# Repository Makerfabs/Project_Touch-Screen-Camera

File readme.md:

# ESP32 3.5" TFT Touch with Camera

```c++
/*
Version:		V6.2
Author:			Vincent
Create Date:	2020/8/19
Note:
	V6.2 : Change Wiki link.
	V6.1 : Update firmware add camera config faq.
	V6.0 : Add WiFi bulletin board demo
	V5.0 : Add Environment Expansion Board
	V4.1 : Add 1 show example.
	V4.0 : Add 4 show example.
	V3.4 : Thanks Lovyan03's change. Greatly speed up the rendering process.
	V3.3 : Change UI direction.
	V3.2 : Added the ability to upload photos to PC through WiFi. 
	V3.1 : Replace the picture with the new hardware.
	V3.0 : Delete many useless code. Add FAQ.
	V2.0 : Change ILI9488 driver,use LovyanGFX lib.Ten times faster than before!!!
	
*/
```
[ESP32 Touch Camera](https://www.youtube.com/watch?v=zWUy4gcwMs4&feature=youtu.be)

[toc]

# Makerfabs

[Makerfabs home page](https://www.makerfabs.com/)

[Makerfabs Wiki](https://wiki.makerfabs.com/)

# ESP32 3.5" TFT Touch with Camera

## Introduce

Product link ：[ ESP32 Touch Camera(Resistive)](https://www.makerfabs.com/esp32-3.5-inch-tft-touch-resistive-with-camera.html) 

Product link ：[ ESP32 Touch Camera(Capacitive)](https://www.makerfabs.com/esp32-3.5-inch-tft-touch-capacitive-with-camera.html) 

Wiki link ：[ESP32 3.5" TFT Touch with Camera](https://wiki.makerfabs.com/ESP32_3.5_TFT_Touch_with_Camera.html) 

The ESP32 Touch Camera use ILI9488 screen, which comes with resistive or capacitive screens. Have an OV2640 camera and SD card slot. It can be used as a webcam, an electronic album, or a digital camera. Support for Arduino and MicroPython. 

## Feature

- Integrated ESP32 2.4G WiFi and Bluetooth.
- Micro SD card slot on board.
- Input 5.0V Type-C USB .
- OV2640 is a 1/4 inch CMOS UXGA (1632*1232) image sensor manufactured by OmniVision.
- LCD 3.5 inch Amorphous-TFT-LCD (Thin Film Transistor Liquid Crystal Display) for mobile-phone or handy electrical equipments.
- NS2009 is A 4-wire resistive touch screen control circuit with I2C interface, which contains A 12-bit resolution A/D converter.

- The FT6X36 Series ICs are single-chip capacitive touch panel controller IC with a built-in 16 bit enhanced Micro-controller unit (MCU).

# Project

## Related projects

[ESP32 2048 GAME](https://github.com/Makerfabs/Project_ESP32-2048GAME)

Implement a 2048 game on "ESP32 Touch Camera". 

[ESP32 Flappy Bird](https://github.com/Makerfabs/Project_ESP32-Flappy-Bird)

Implement a Flappy Bird game on "ESP32 Touch Camera". 

## Project introduction

Four projects were implemented : "Camera", "Touch_Draw", "SD2TFT" and "Receive WiFi Video".

### Camera_V2

- Take photos with OV2640 camera and preview in real-time on TFT screen.
- You can save photos to an SD card.
- Photos taken can be viewed through the TFT screen.

### Touch_Draw_V2

- Use your hand or stylus (resistance screen) to draw on the screen.

### SD2TFT 

- Display pictures from SD card.
- Loop back the images in the SD card.

### Receive WiFi Video

Transmit the contents of the monitor to the TFT screen via Wifi.A host computer software is provided to box select the areas of the screen that need to be transferred.

Change from [MakePython ESP32 Color LCD で 動画をWiFi受信](https://homemadegarbage.com/makerfabs05)

- Upload file : "/Project_Touch-Screen-Camra/ESP32_ScreenShotReceiver-master/ScreenShotReceiver/ScreenShotReceiver.ino"
- Open "/Project_Touch-Screen-Camra/ESP32_ScreenShotReceiver-master/ScreenShotSender.exe"
- Input IP on the screen.

- Push connect.
- Start share your screen to TFT.

## Compiler Options

**If you have any questions，such as how to install the development board, how to download the code, how to install the library. Please refer to :[Makerfabs_FAQ](https://github.com/Makerfabs/Makerfabs_FAQ)**

- Install board : ESP32 , select ESP32 version 1.0.6!!!!!!! After 2.0.0 version can't run successfully.
- **2022/4/28 Add：I don't know which libraries I updated, 1.0.6 compiles but doesn't drive the camera properly, rolling back the ESP32 version to 1.0.5 works fine.**
- Install library : LovyanGFX library. (SD2TFT is use a different GFX lib, depend on Adafruit_GFX. )
- Edit the code based on the touch screen. If you use resistive screen, choice NS2009_TOUCH. If you use capacitive screen, choice FT6236_TOUCH.

```c++
#define NS2009_TOUCH        //Resistive screen driver    
//#define FT6236_TOUCH      //Capacitive screen driver

#ifdef NS2009_TOUCH
#include "NS2009.h"
const int i2c_touch_addr = NS2009_ADDR;
#endif

#ifdef FT6236_TOUCH
#include "FT6236.h"
const int i2c_touch_addr = TOUCH_I2C_ADD;
#endif

```

- Upload codes, select "ESP32 Wrover Module" and "Huge APP"

- Insert a Micro SD card into ESP32 Touch Camera.

## How To Use ESP32 Touch Camera

- Open the serial port monitor after uploading the code.
- Serial port will return initialization information, pay attention to see if there is any error.

```txt
14:48:49.096 -> ets Jun  8 2016 00:22:57
14:48:49.096 -> 
14:48:49.096 -> rst:0x1 (POWERON_RESET),boot:0x17 (SPI_FAST_FLASH_BOOT)
14:48:49.096 -> configsip: 0, SPIWP:0xee
14:48:49.096 -> clk_drv:0x00,q_drv:0x00,d_drv:0x00,cs0_drv:0x00,hd_drv:0x00,wp_drv:0x00
14:48:49.096 -> mode:DIO, clock div:1
14:48:49.096 -> load:0x3fff0018,len:4
14:48:49.096 -> load:0x3fff001c,len:1100
14:48:49.096 -> load:0x40078000,len:9232
14:48:49.096 -> load:0x40080400,len:6400
14:48:49.096 -> entry 0x400806a8
14:48:50.641 -> ILI9488 Test!
14:48:50.641 -> I2C device found at address 0x38  !
14:48:50.675 -> Card Mount Successed
14:48:50.675 -> SD init over.
14:48:51.397 -> TFT init over.
14:49:10.660 -> Image name：/0write.bmp
14:49:13.859 -> Image name：/1write.bmp

```

- If the SD card cannot be mounted on return, you need to re-insert the SD card.
- If everything is normal, the camera interface will be displayed.

- Press the camera button to take photos automatically.
- Click on the previous photo to show the last photo saved on the SD card.

- Pressing to show the last photo will stop the camera acquisition. To restore the preview, press open Stream.
- Restore stream mode to take photos again.
- You can unplug your SD card and plug it into your computer to view your photos.

## V3.2 Upload photos via WiFi
Added the function of sending photos to PC via HTTP protocol by post method.
- Remove comments before WIFI_MODE

```c++
#define WIFI_MODE
```
- Set the wifi ssid and password.

```c++
// wait for WiFi connection
WiFi.mode(WIFI_STA);
WiFi.begin("Makerfabs", "20160704");
```
- Upload code to ESP32 camera.
- Run the server.py  on PC side.(Make sure to run in the directory server.py, otherwise the upload path cannot be found.)

- Every time you click to show the last photo, it will be automatically uploaded.

- In a few seconds, the picture will be uploaded to the Upload folder.
- V3.3  :  The UI has changed, but the functionality remains the same.

## V4.0 Show Example

Add 4 example in /Project_Touch-Screen-Camra/example

- Aht10 show
- HCSR04 meter
- Web button
- Wind speed show

These examples depend on TFT_eSPI library. You must set "User_Setup.h".
Set screen type.

```c++
// Only define one driver, the other ones must be commented out
//#define ILI9341_DRIVER
//#define ST7735_DRIVER      // Define additional parameters below for this display
//#define ILI9163_DRIVER     // Define additional parameters below for this display
//#define S6D02A1_DRIVER
//#define RPI_ILI9486_DRIVER // 20MHz maximum SPI
//#define HX8357D_DRIVER
//#define ILI9481_DRIVER
//#define ILI9486_DRIVER
#define ILI9488_DRIVER     // WARNING: Do not connect ILI9488 display SDO to MISO if other devices share the SPI bus (TFT SDO does NOT tristate when CS is high)
//#define ST7789_DRIVER      // Full configuration option, define additional parameters below for this display
//#define ST7789_2_DRIVER    // Minimal configuration option, define additional parameters below for this display

// For ST7789, ST7735, ILI9163 and GC9A01 ONLY, define the pixel width and height in portrait orientation
// #define TFT_WIDTH  80
// #define TFT_WIDTH  128
// #define TFT_WIDTH  172 // ST7789 172 x 320
//#define TFT_WIDTH  240 // ST7789 240 x 240 and 240 x 320
#define TFT_WIDTH  320
// #define TFT_HEIGHT 160
// #define TFT_HEIGHT 128
// #define TFT_HEIGHT 240 // ST7789 240 x 240
// #define TFT_HEIGHT 320 // ST7789 240 x 320
//#define TFT_HEIGHT 240 // GC9A01 240 x 240
#define TFT_HEIGHT 480

```
And set pins.

```c++
// For 3.5" 9488
// The hardware SPI can be mapped to any pins

#define TFT_MISO 12
#define TFT_MOSI 13
#define TFT_SCLK 14
#define TFT_CS   15  // Chip select control pin
#define TFT_DC    33  // Data Command control pin
#define TFT_RST   26  // Reset pin (could connect to RST pin)

```

## V4.1 Show Example

Add environment monitoring module demo.

- Line chart

## V6.0 WiFi bulletin board Demo

Added a WiFi bulletin board app. You can upload and browse files in the SD card through the web page. And the latest uploaded BMP or TXT display on the 3.5-inch screen.

- Library Install：[esp32-micro-sdcard](https://github.com/nhatuan84/esp32-micro-sdcard) and [esp32-webserver](https://github.com/nhatuan84/esp32-webserver)
- Upload .\example\wifi_img\wifi_img.ino
- Insert the SD card and power on.
- Enter the IP address on the screen in your browser.

- Select TXT or BMP to be uploaded. BMP must be 480 x 320 pixels, 24 bits.

- Upload.
- Wait seconds, the content is displayed on the screen.

## FAQ

### Q: Can't Upload!

A: Switch to a good USB cable. Poor USB cable quality can cause ESP32 to reboot or fail to upload. Open the serial monitor, observe serial port information.

### Q: The screen is white!

A: The SD card was not mounted successfully, so the program goes into an endless loop. Re-insert the SD card and restart it. Open the serial monitor,  The serial port will display the work log.

### Q: It doesn't show the picture that was just taken!

A: It may be that after shooting, the SD card was not in good contact, so it could not be stored in the SD card. Playback photos are read inside the SD card photos. Re-insert the SD card and restart it.

### Q: Other questions...

A: Re-insert the SD card and restart it. Can solve most problems. (laugh)

### Q: Camera direction wrong

A: Depending on the batch of purchased cameras, the picture may be inverted. You can configure the following functions.

Change set_vflip() param to flip camera or set_hmirror() to mirror image.

```c++
// Camera setting
void camera_init()
{
    // camera config
    
    //...

    sensor_t *s = esp_camera_sensor_get();
    // initial sensors are flipped vertically and colors are a bit saturated
    if (s->id.PID == OV2640_PID)
    {
        s->set_vflip(s, 0);   // vertical flip
        s->set_hmirror(s, 0); // Horizontal mirror

        s->set_brightness(s, 0); // up the blightness just a bit
        s->set_saturation(s, 1); // lower the saturation
    }
    // drop down frame size for higher initial frame rate
    s->set_framesize(s, FRAMESIZE_QVGA);

    show_log(2);
}
```

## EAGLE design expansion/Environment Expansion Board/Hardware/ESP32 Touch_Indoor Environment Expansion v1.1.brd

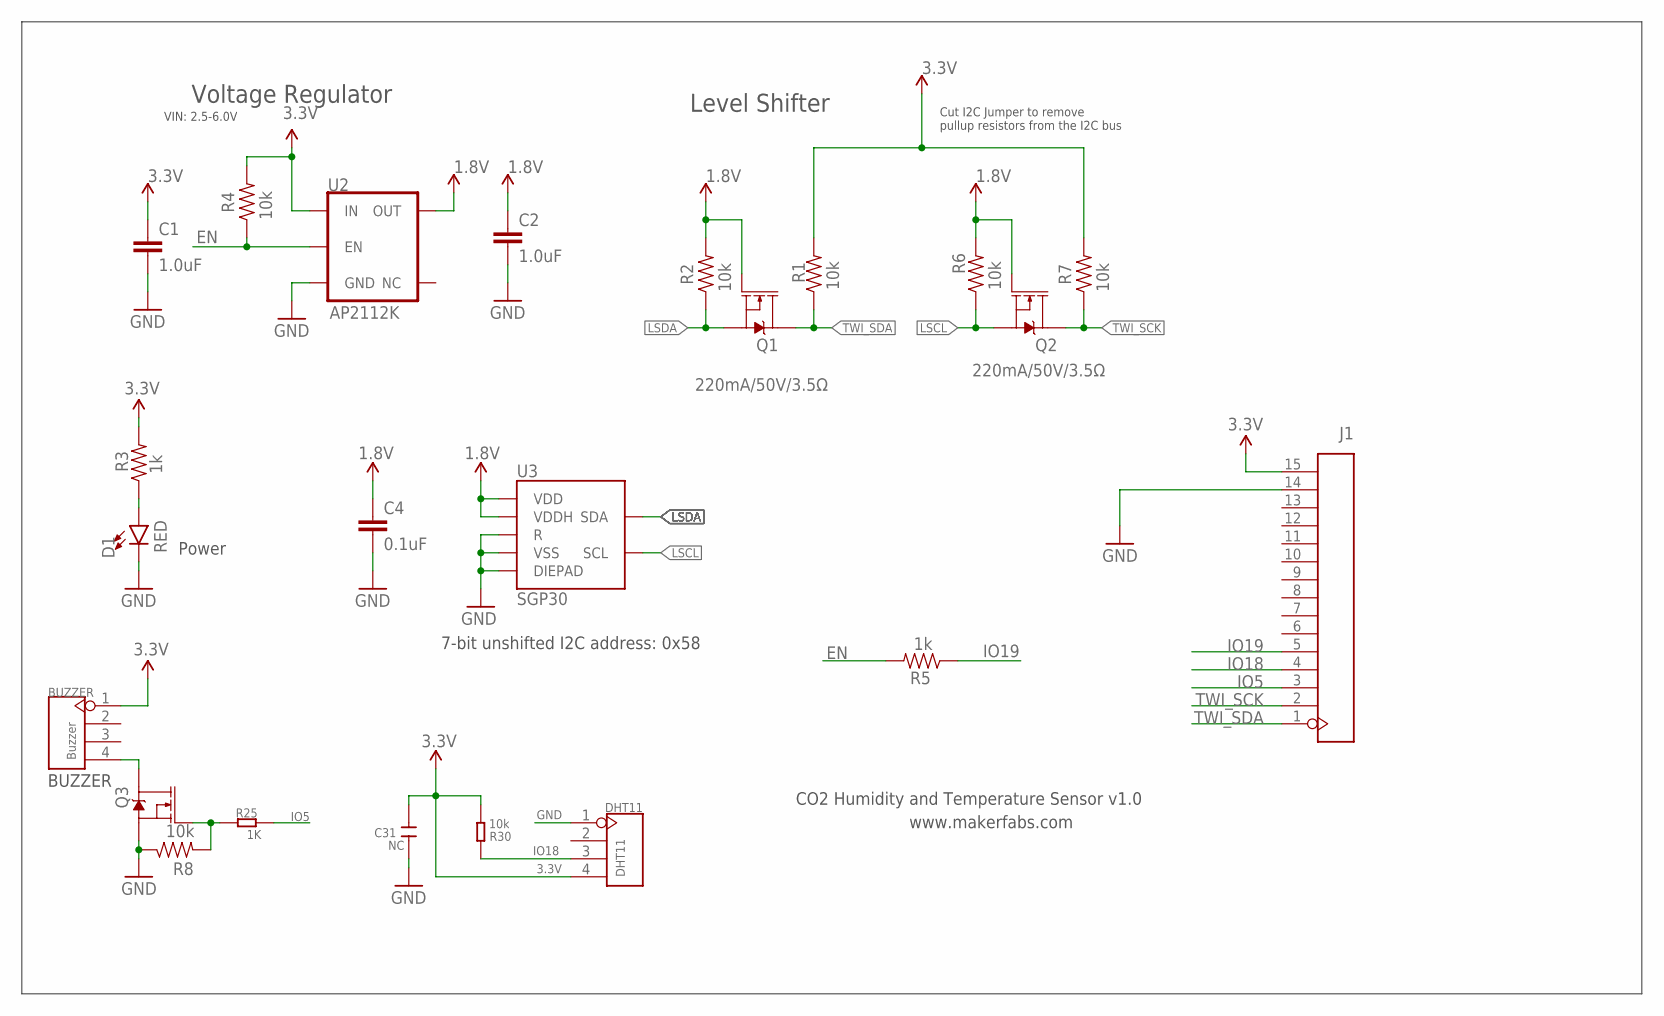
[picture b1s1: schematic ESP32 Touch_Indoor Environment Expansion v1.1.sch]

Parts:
BUZZER: Buzzer; 4P-65/35ROUND
C1, C2: 1.0uF; 0603
C4: 0.1uF; 0603
C31: NC; 0603
D1: RED; LED-0603
DHT11: DHT11; 4P-65/35ROUND
J1: HEADER-1X15P3; DIP-1X15-2.54MM-W
Q1, Q2, Q3: 220mA/50V/3.5Ω; SOT23-3
R1, R2, R4, R6, R7, R8: 10k; 0603
R3, R5: 1k; 0603
R25: 1K; R0603
R30: 10k; R0603
U2: AP2112K; SOT23-5
U3: SGP30

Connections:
1.8V: C2.1, C4.1, Q1.1 (G), Q2.1 (G), R2.2, R6.2, U2.5 (OUT), U3.1 (VDD), U3.5 (VDDH)
3.3V: BUZZER.1, C1.1, C31.2, DHT11.4, J1.15, R1.2, R3.2, R4.2, R7.2, R30.2, U2.1 (IN)
EN: R4.1, R5.2, U2.3 (EN)
GND: C1.2, C2.2, C4.2, C31.1, D1.C, DHT11.1, J1.14, Q3.2 (S), R8.1, U2.2 (GND), U3.2 (VSS), U3.4 (R), U3.DIEPAD
IO5: J1.3, R25.1
IO18: DHT11.3, J1.4, R30.1
IO19: J1.5, R5.1
LSCL: Q2.2 (S), R6.1, U3.6 (SCL)
LSDA: Q1.2 (S), R2.1, U3.3 (SDA)
unnamed: BUZZER.4, Q3.3 (D)
unnamed: Q3.1 (G), R8.2, R25.2
unnamed: D1.A, R3.1
TWI_SCK: J1.2, Q2.3 (D), R7.1
TWI_SDA: J1.1, Q1.3 (D), R1.1

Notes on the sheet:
Voltage Regulator
VIN: 2.5-6.0V
Cut I2C Jumper to remove pullup resistors from the I2C bus
Power
7-bit unshifted I2C address: 0x58
CO2 Humidity and Temperature Sensor v1.0
www.makerfabs.com
Level Shifter
BUZZER

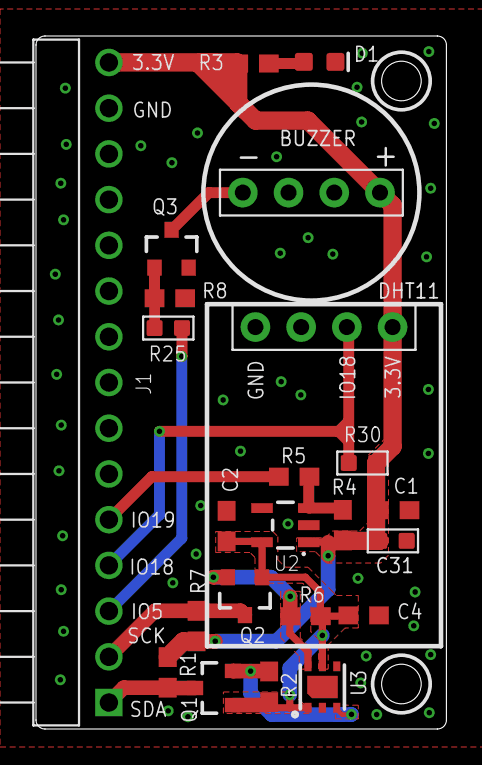
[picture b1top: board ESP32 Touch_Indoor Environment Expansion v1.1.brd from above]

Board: 2 copper layers, 22.8 x 38.5 mm, 24 parts (1 on the bottom side), 14 nets.

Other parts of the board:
U$1: MAKERFABS_0.3

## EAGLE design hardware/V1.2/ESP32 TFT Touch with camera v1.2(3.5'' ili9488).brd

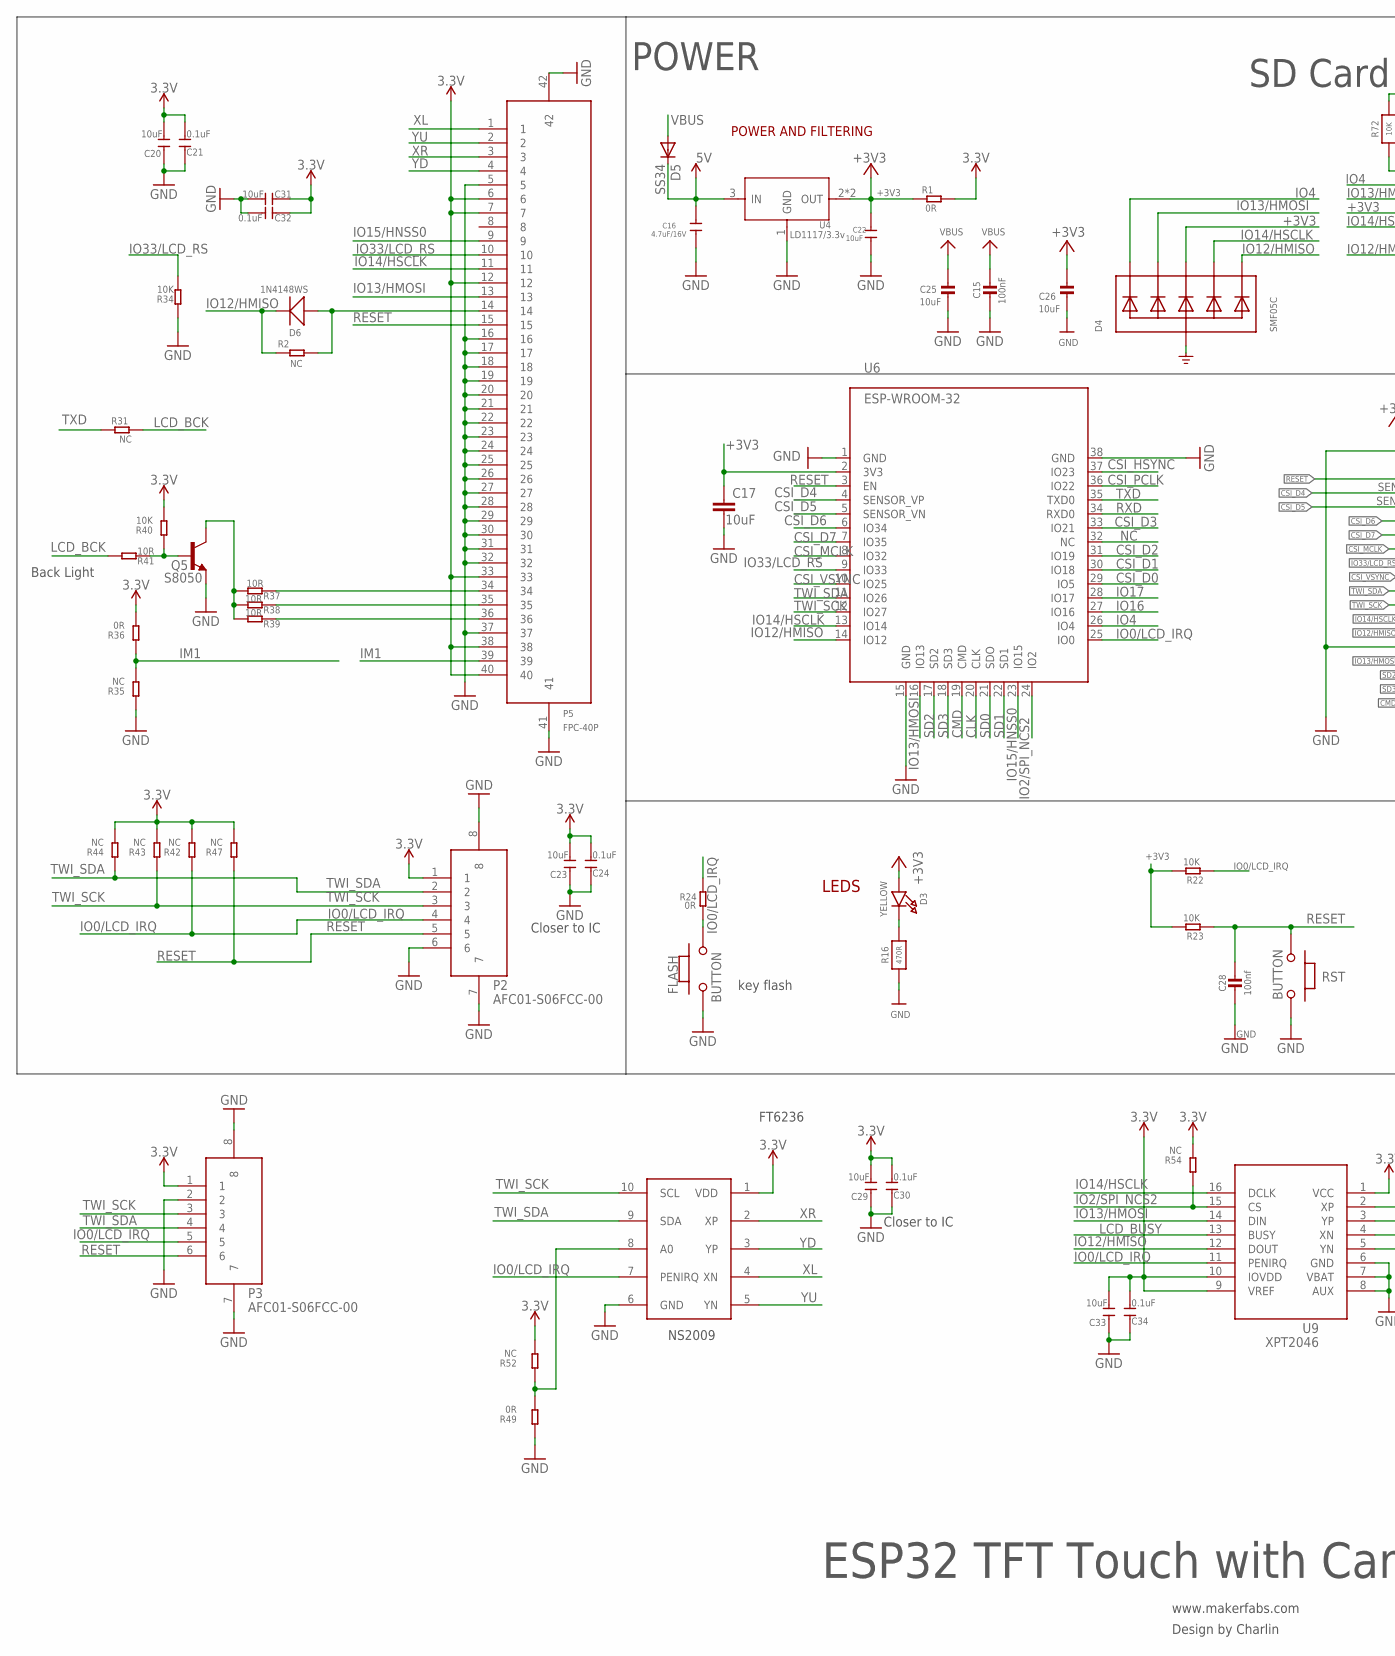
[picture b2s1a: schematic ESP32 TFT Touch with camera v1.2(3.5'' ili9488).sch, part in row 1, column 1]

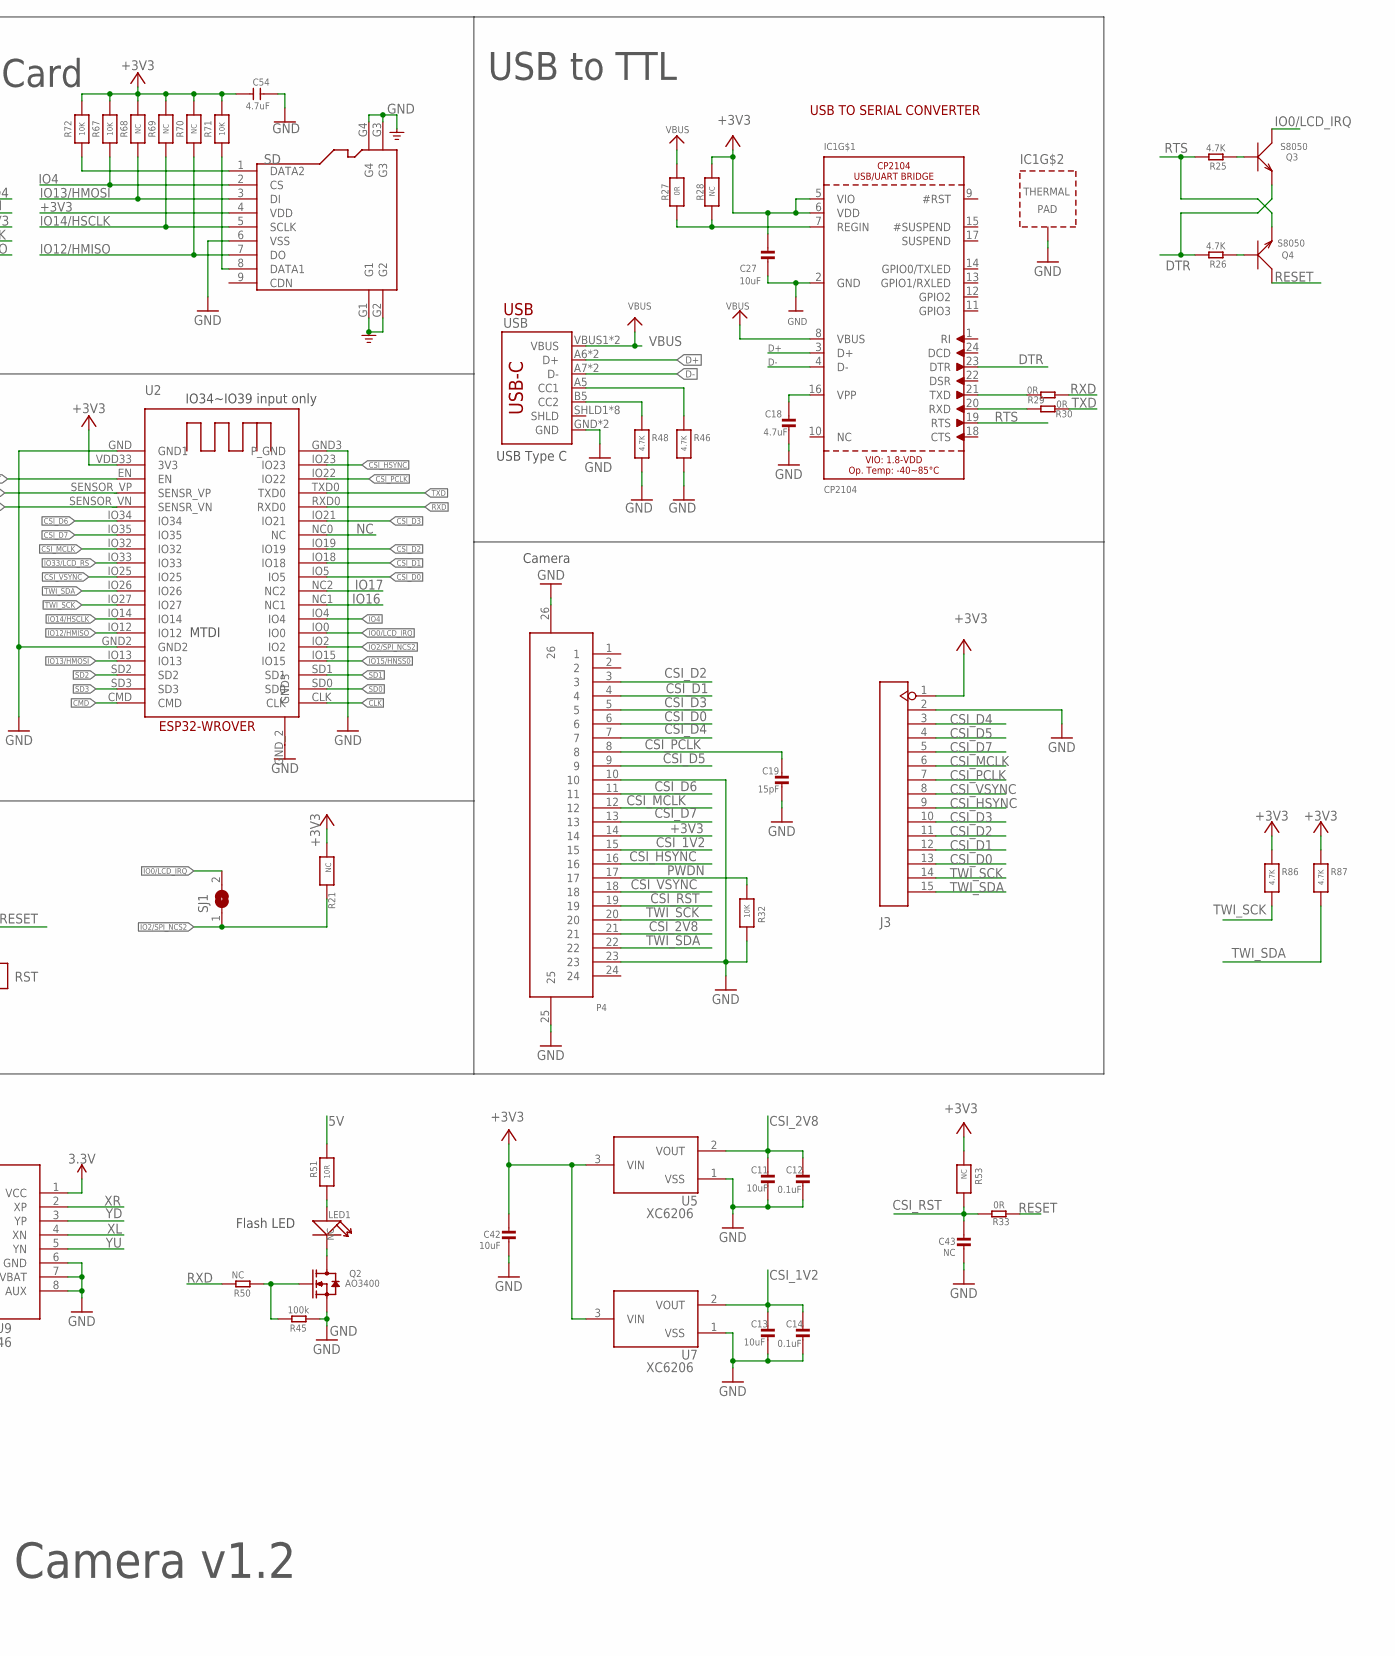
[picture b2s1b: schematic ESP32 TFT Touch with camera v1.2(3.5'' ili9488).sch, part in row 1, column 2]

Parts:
C11, C13, C25, C26, C27, C42: 10uF; 0603-NO
C12, C14: 0.1uF; 0603-NO
C15: 100nF; 0603-NO
C16: 4.7uF/16V; 0603
C17: 10uF; C0603
C18: 4.7uF; 0603-NO
C19: 15pF; 0603-NO
C20, C23, C29, C31, C33: 10uF; DISCRETE_C0603
C21, C24, C30, C32, C34: 0.1uF; DISCRETE_C0603
C22: 10uF; 0603
C28: 100nf; 0603-NO
C43: NC; 0603-NO
C54: 4.7uF; DISCRETE_C0603
D3: YELLOW; CHIPLED_0805_NOOUTLINE
D4: SMF05C; SOT363
D5: SS34; DO-214AC
D6: 1N4148WS; SOD323
FLASH: BUTTON; 157SW
IC1: CP2104; QFN24_4MM_SMSC
J3: HEADER-1X15P; SMD15-2.54P8.5H
LED1: NC; DISCRETE_LED-3528
P2, P3: AFC01-S06FCC-00; SMD8-50P-740L535W
P4: FPC-24P; SMD26-50P-1760L450W
P5: FPC-40P; SMD42-50P-2560L490W
Q2: AO3400; SOT23@1
Q3, Q4: S8050; SOT23
Q5: S8050; SPARKFUN_SOT23
R1, R24, R29, R30, R33: 0R; R0603
R2, R31, R50: NC; R0603
R16: 470R; 0603-NO
R21, R28, R53, R68, R69, R70: NC; 0603-NO
R22, R23: 10K; R0603
R25, R26: 4.7K; R0603
R27: 0R; 0603-NO
R32, R67, R71, R72: 10K; 0603-NO
R34, R40: 10K; DISCRETE_R0603
R35, R42, R43, R44, R47, R52, R54: NC; DISCRETE_R0603
R36, R49: 0R; DISCRETE_R0603
R37, R38, R39, R41: 10R; DISCRETE_R0603
R45: 100k; R0603
R46, R48, R86, R87: 4.7K; 0603-NO
R51: 10R; 0603-NO
RST: BUTTON; 157SW
SD: HOLDER-MICROSD-9P; 9P-SMD-W/-RING
SJ1: SJ
U2: ESP32-WROVER
U4: LD1117/3.3v; SOT89
U5, U7: XC6206; SOT-23
U6: ESP-WROOM-32
U8: NS2009; MSOP10
U9: XPT2046; TSSOP16-65P-560L910W
USB: USB_C5; USB-C-16P-5

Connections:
3.3V: C20.2, C21.2, C23.2, C24.2, C29.2, C30.2, C31.1, C32.1, C33.2, C34.2, P2.1, P3.1, P5.6, P5.7, P5.12, P5.33, P5.38, P5.40, R1.2, R36.2, R40.2, R42.2, R43.2, R44.2, R47.2, R52.2, R54.2, U8.1 (VDD), U9.1 (VCC), U9.9 (VREF), U9.10 (IOVDD)
5V: C16.1, D5.C, R51.1, U4.3 (IN)
+3V3: C17.1, C22.1, C26.1, C27.1, C42.1, C54.2, D3.A, D4.4 (C3), IC1.5 (VIO), IC1.6 (VDD), J3.1, P4.14, R1.1, R21.1, R22.2, R23.2, R28.1, R53.1, R67.2, R68.2, R69.2, R70.2, R71.2, R72.2, R86.1, R87.1, SD.4 (VDD), U2.VDD33 (3V3), U4.2 (OUT), U4.4 (OUT), U5.3 (VIN), U6.2 (3V3), U7.3 (VIN)
CLK: U2.CLK, U6.20 (CLK)
CMD: U2.CMD, U6.19 (CMD)
CSI_1V2: C13.1, C14.1, P4.15, U7.2 (VOUT)
CSI_2V8: C11.1, C12.1, P4.21, U5.2 (VOUT)
CSI_D0: J3.13, P4.6, U2.IO5, U6.29 (IO5)
CSI_D1: J3.12, P4.4, U2.IO18, U6.30 (IO18)
CSI_D2: J3.11, P4.3, U2.IO19, U6.31 (IO19)
CSI_D3: J3.10, P4.5, U2.IO21, U6.33 (IO21)
CSI_D4: J3.3, P4.7, U2.SENSOR_VP (SENSR_VP), U6.4 (SENSOR_VP)
CSI_D5: J3.4, P4.9, U2.SENSOR_VN (SENSR_VN), U6.5 (SENSOR_VN)
CSI_D6: P4.11, U2.IO34, U6.6 (IO34)
CSI_D7: J3.5, P4.13, U2.IO35, U6.7 (IO35)
CSI_HSYNC: J3.9, P4.16, U2.IO23, U6.37 (IO23)
CSI_MCLK: J3.6, P4.12, U2.IO32, U6.8 (IO32)
CSI_PCLK: C19.1, J3.7, P4.8, U2.IO22, U6.36 (IO22)
CSI_RST: C43.1, P4.19, R33.2, R53.2
CSI_VSYNC: J3.8, P4.18, U2.IO25, U6.10 (IO25)
D+: IC1.3 (D+), USB.A6 (D+), USB.B6 (D+)
D-: IC1.4 (D-), USB.A7 (D-), USB.B7 (D-)
DTR: IC1.23 (DTR), Q3.2 (E), R26.2
GND: C11.2, C12.2, C13.2, C14.2, C15.2, C16.2, C17.2, C18.2, C19.2, C20.1, C21.1, C22.2, C23.1, C24.1, C25.2, C26.2, C27.2, C28.2, C29.1, C30.1, C31.2, C32.2, C33.1, C34.1, C42.2, C43.2, C54.1, D4.2 (A), FLASH.1, IC1.2 (GND), IC1.THERM (TP), J3.2, P2.6, P2.7, P2.8, P3.2, P3.7, P3.8, P4.10, P4.23, P4.25, P4.26, P5.5, P5.16, P5.17, P5.18, P5.19, P5.20, P5.21, P5.22, P5.23, P5.24, P5.25, P5.26, P5.27, P5.28, P5.29, P5.30, P5.31, P5.32, P5.37, P5.41, P5.42, Q2.2 (S), Q5.2 (E), R16.1, R32.2, R34.1, R35.1, R45.1, R46.2, R48.2, R49.1, RST.1, SD.6 (VSS), SD.G1, SD.G2, SD.G3, SD.G4, U2.GND (GND1), U2.GND2, U2.GND3 (P_GND), U2.GND_2 (GND3), U4.1 (GND), U5.1 (VSS), U6.1 (GND), U6.15 (GND), U6.38 (GND), U7.1 (VSS), U8.6 (GND), U9.6 (GND), U9.7 (VBAT), U9.8 (AUX), USB.GND, USB.GND2 (GND)
IM1: P5.39, R35.2, R36.1
IO0/LCD_IRQ: P2.4, P3.5, Q3.3 (C), R22.1, R24.2, R42.1, SJ1.2, U2.IO0, U6.25 (IO0), U8.7 (PENIRQ), U9.11 (PENIRQ)
IO2/SPI_NCS2: R21.2, R54.1, SJ1.1, U2.IO2, U6.24 (IO2), U9.15 (CS)
IO4: D4.1 (C1), R67.1, SD.2 (CS), U2.IO4, U6.26 (IO4)
IO12/HMISO: D4.6 (C5), D6.-, R2.1, R70.1, SD.7 (DO), U2.IO12, U6.14 (IO12), U9.12 (DOUT)
IO13/HMOSI: D4.3 (C2), P5.13, R68.1, SD.3 (DI), U2.IO13, U6.16 (IO13), U9.14 (DIN)
IO14/HSCLK: D4.5 (C4), P5.11, R69.1, SD.5 (SCLK), U2.IO14, U6.13 (IO14), U9.16 (DCLK)
IO15/HNSS0: P5.9, U2.IO15, U6.23 (IO15)
IO16: U2.NC1, U6.27 (IO16)
IO17: U2.NC2, U6.28 (IO17)
IO33/LCD_RS: P5.10, R34.2, U2.IO33, U6.9 (IO33)
LCD_BCK: R31.2, R41.2
LCD_BUSY: U9.13 (BUSY)
unnamed: C18.1, IC1.16 (VPP)
unnamed: Q4.1 (B), R26.1
unnamed: Q3.1 (B), R25.1
unnamed: D6.+, P5.14, R2.2
unnamed: Q2.1 (G), R45.2, R50.1
unnamed: FLASH.2, R24.1
unnamed: D3.C, R16.2
unnamed: LED1.1 (+), R51.2
unnamed: LED1.2 (-), Q2.3 (D)
unnamed: R46.1, USB.A5 (CC1)
unnamed: R48.1, USB.B5 (CC2)
unnamed: IC1.7 (REGIN), R27.2, R28.2
unnamed: IC1.21 (TXD), R29.2
unnamed: IC1.20 (RXD), R30.2
unnamed: P5.34, R37.1
unnamed: P5.35, R38.1
unnamed: P5.36, R39.1
unnamed: Q5.1 (B), R40.1, R41.1
unnamed: Q5.3 (C), R37.2, R38.2, R39.2
unnamed: R49.2, R52.1, U8.8 (A0)
unnamed: R72.1, SD.1 (DATA2)
unnamed: R71.1, SD.8 (DATA1)
NC: U2.NC0 (NC), U6.32 (NC)
PWDN: P4.17, R32.1
RESET: C28.1, P2.5, P3.6, P5.15, Q4.3 (C), R23.1, R33.1, R47.1, RST.2, U2.EN, U6.3 (EN)
RTS: IC1.19 (RTS), Q4.2 (E), R25.2
RXD: R29.1, R50.2, U2.RXD0, U6.34 (RXD0)
SD0: U2.SD0, U6.21 (SDO)
SD1: U2.SD1, U6.22 (SD1)
SD2: U2.SD2, U6.17 (SD2)
SD3: U2.SD3, U6.18 (SD3)
TWI_SCK: J3.14, P2.3, P3.3, P4.20, R43.1, R86.2, U2.IO27, U6.12 (IO27), U8.10 (SCL)
TWI_SDA: J3.15, P2.2, P3.4, P4.22, R44.1, R87.2, U2.IO26, U6.11 (IO26), U8.9 (SDA)
TXD: R30.1, R31.1, U2.TXD0, U6.35 (TXD0)
VBUS: C15.1, C25.1, D5.A, IC1.8 (VBUS), R27.1, USB.VBUS1 (VBUS), USB.VBUS2 (VBUS)
XL: P5.1, U8.4 (XN), U9.4 (XN)
XR: P5.3, U8.2 (XP), U9.2 (XP)
YD: P5.4, U8.3 (YP), U9.3 (YP)
YU: P5.2, U8.5 (YN), U9.5 (YN)

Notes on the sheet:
www.makerfabs.com
Design by Charlin
USB
LEDS
POWER AND FILTERING
USB TO SERIAL CONVERTER
key flash
ESP32 TFT Touch with Camera v1.2
MTDI
IO34~IO39 input only
POWER
USB to TTL
USB Type C
SD Card
Flash LED
Camera
NS2009
FT6236
Closer to IC
Back Light

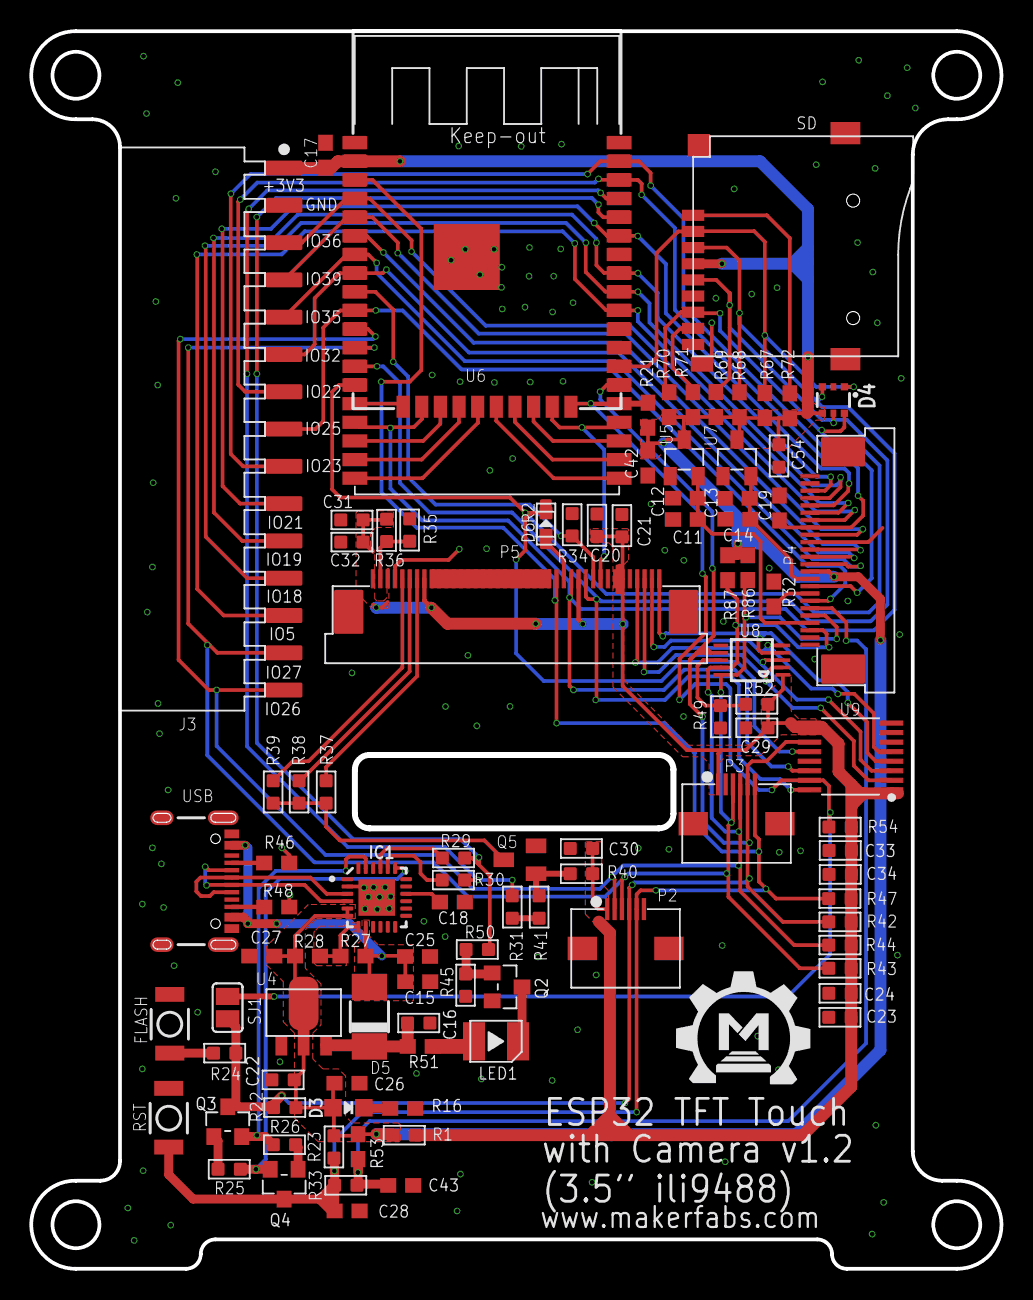
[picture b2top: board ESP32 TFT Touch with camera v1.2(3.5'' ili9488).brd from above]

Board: 2 copper layers, 66.1 x 84.3 mm, 100 parts (0 on the bottom side), 75 nets.

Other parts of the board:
U$1: MAKERFABS_0.3

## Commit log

2020-08-12 create project
2020-08-12 ns2009
2020-08-12 touch test
2020-08-14 resistor screen draw
2020-08-14 capacitance screen
2020-08-17 9488 error
2020-08-17 Show sd picture
2020-08-18 read sd picture ok
2020-08-18 ns2009 already
2020-08-18 Rebuid touch driver
2020-08-19 ov2640 show on tft
2020-08-20 a simple camera
2020-08-21 finish v1.0
2020-08-21 add sd card speed
2020-08-21 edit readme
2020-08-25 repair ft6236
2020-08-29 draw bug repair
2020-09-03 change ILI9488 driver,more faster
2020-09-04 add wifi screen
2020-09-07 add youtube url
2020-09-10 repair bug
2020-09-10 repair ns2009 bug
2020-09-11 v3.0
2020-09-15 There is a bug with NS2009, fix it.
2020-09-15 Replace new picture
2020-09-15 add picture
2020-09-15 add hardware
2020-09-15 add relate project
2020-09-16 add product link
2020-09-22 add wifi upload
2020-09-25 Change UI
2020-09-25 chang new camera ui
2020-11-12 update: Improving the rendering speed of camera images. update: Fixed the bitmap header.
2020-12-24 Add a sd card test
2020-12-25 Added SD card exception display
2020-12-28 Add sd_test LCD spi init.
2020-12-29 Add ns2009 touch
2020-12-31 Try lovyan's code and delete some useless code.
2020-12-31 Speed up screen
2020-12-31 Thanks Lovyan03'change,greatly speed up.
2021-01-03 Add code description
2021-03-18 change SCH to V1.2
2021-04-06 V4.0 add example
2021-04-07 Add example instruction.
2021-05-06 V4.1 add exmaple
2021-05-21 V5.0 Add Environment Expansion Board
2021-07-16 Create TDS meter
2021-09-07 Create LVGL
2021-09-14 create datasheet
2021-09-14 Fix bug
2021-09-23 add datasheet
2021-10-26 V6.0 Wifi Img Display Demo
2022-04-28 V6.1 update firmware

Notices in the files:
parts and their libraries:
SparkFun-IC-Power: Licensing: Creative Commons ShareAlike 4.0 International - https://creativecommons.org/licenses/by-sa/4.0
microbuilder: This work is placed in the public domain, and may be freely used for commercial and non-commercial work with the following conditions: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
